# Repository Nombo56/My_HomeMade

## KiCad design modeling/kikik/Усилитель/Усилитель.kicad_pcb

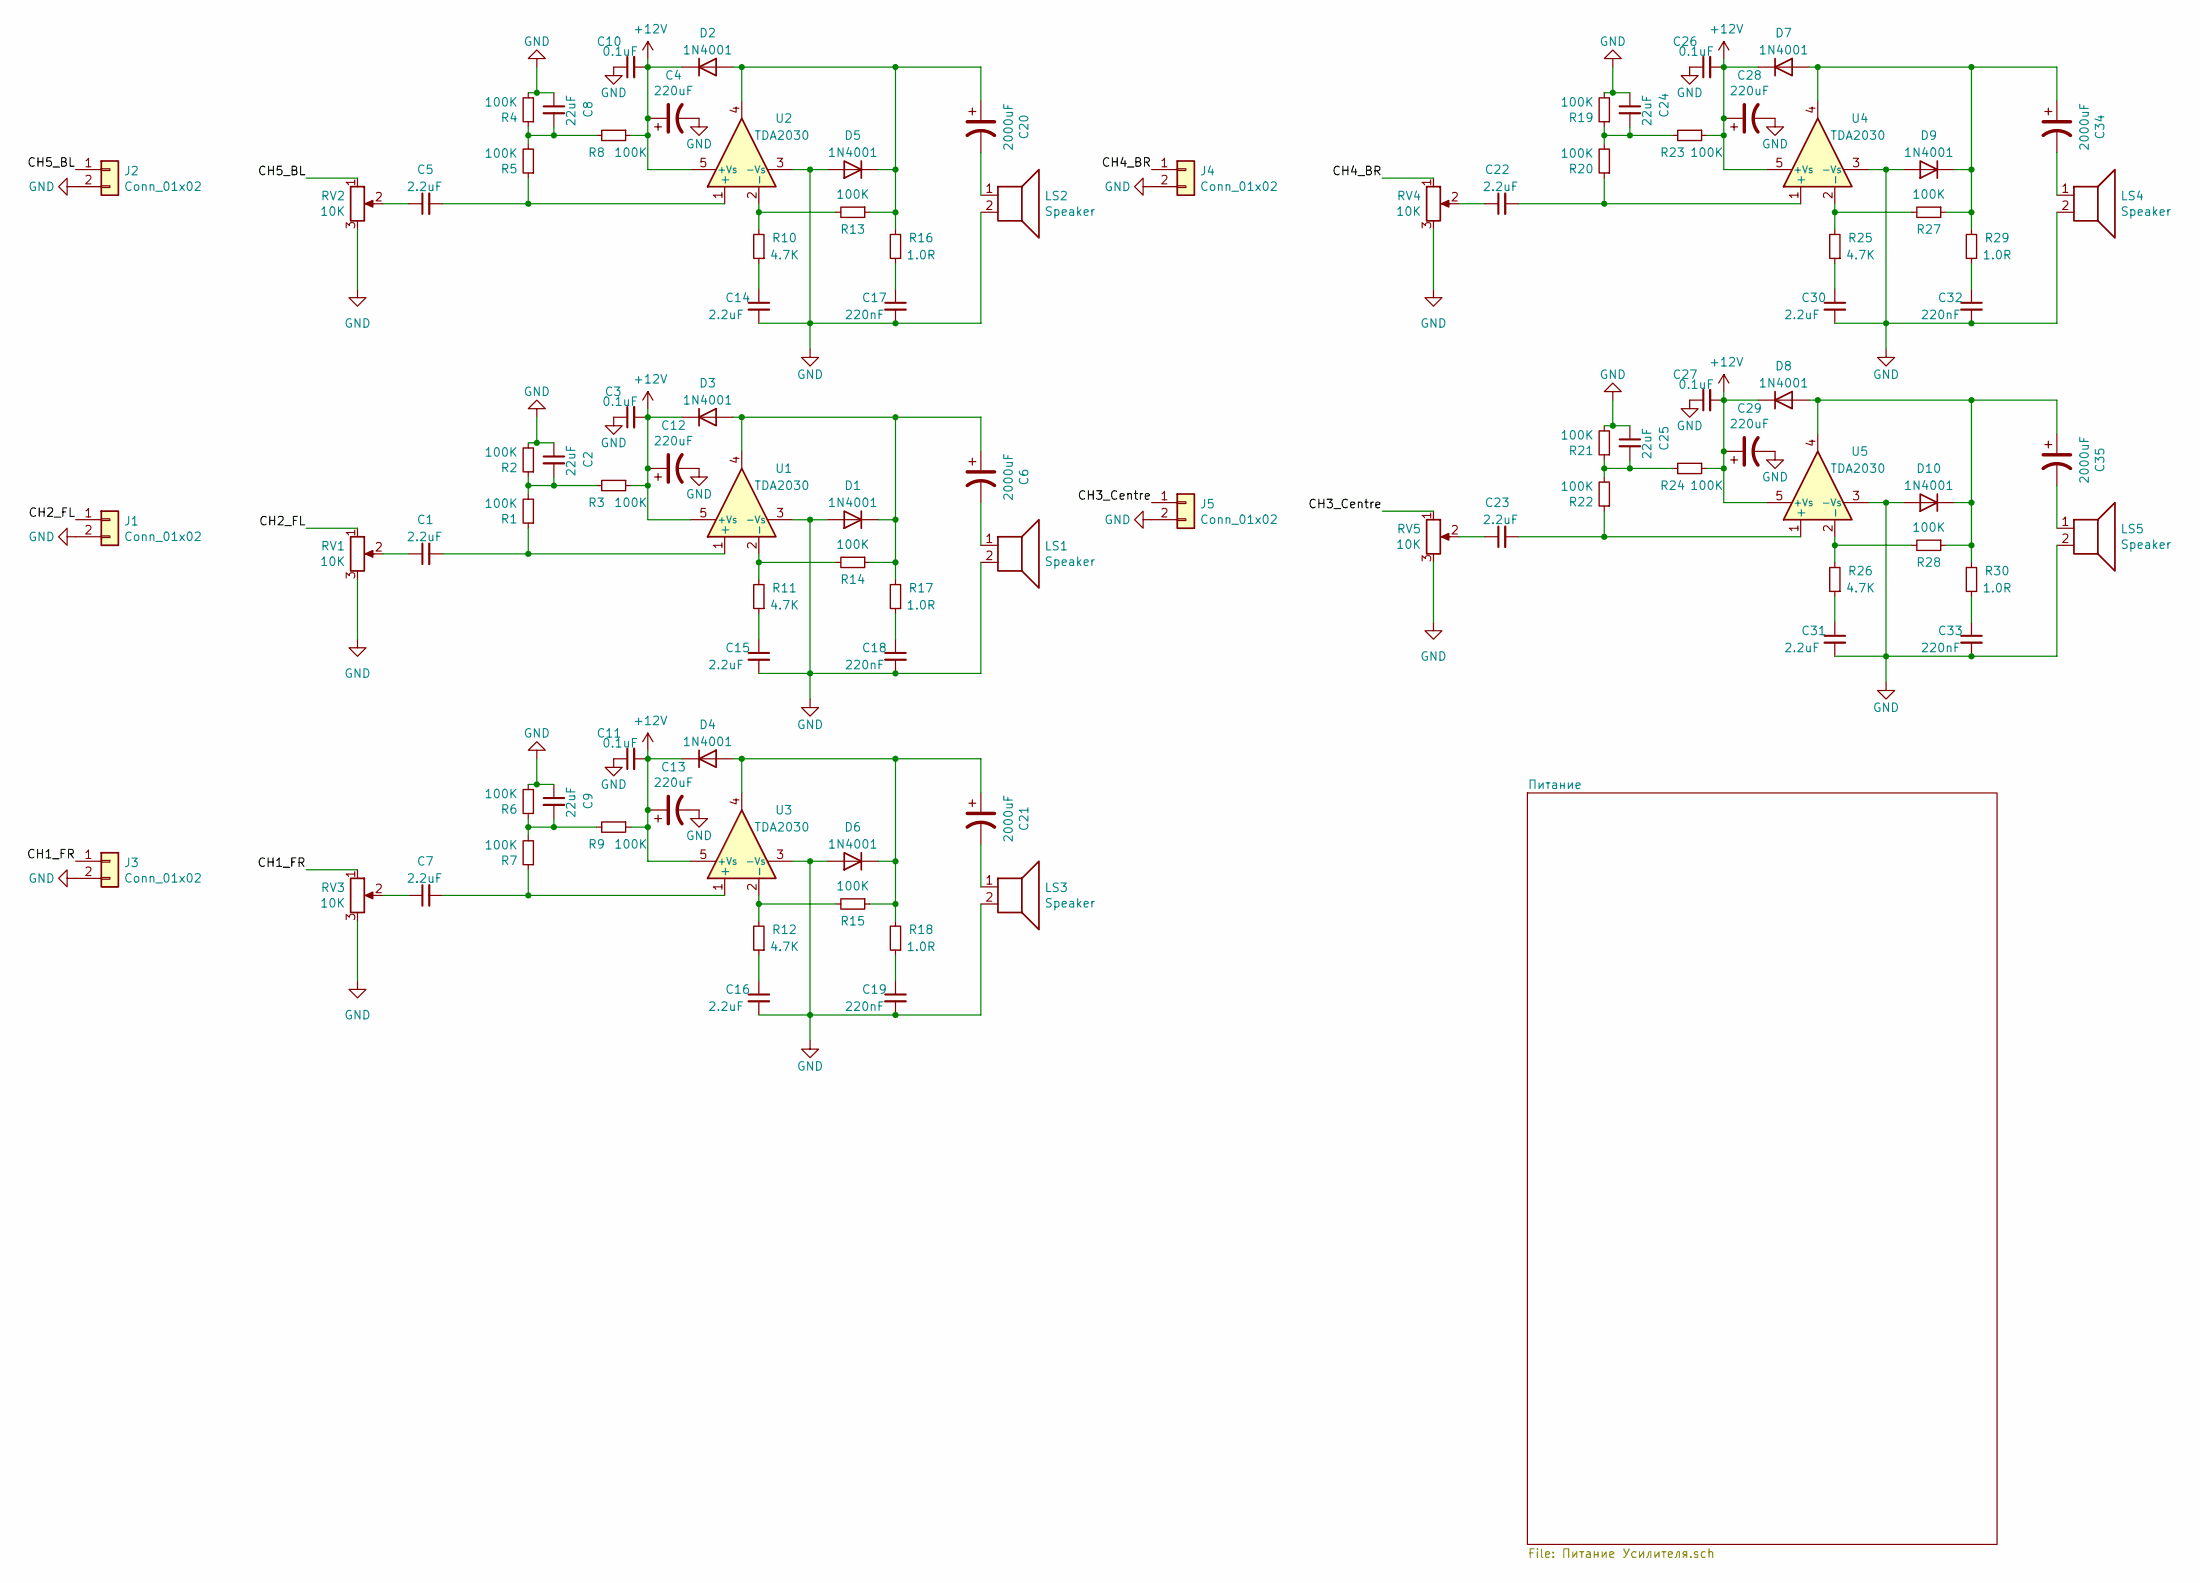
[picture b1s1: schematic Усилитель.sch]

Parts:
C1, C5, C7, C14, C15, C16, C22, C23, C30, C31: 2.2uF; C_0805_2012Metric
C2, C8, C9, C24, C25: 22uF; C_0805_2012Metric
C3, C10, C11, C26, C27: 0.1uF; C_0805_2012Metric
C4, C12, C13, C28, C29: 220uF; C_Elec_8x10.2
C6, C20, C21, C34, C35: 2000uF; CP_Radial_D13.0mm_P5.00mm
C17, C18, C19, C32, C33: 220nF; C_0805_2012Metric
D1, D2, D3, D4, D5, D6, D7, D8, D9, D10: 1N4001; D_DO-41_SOD81_P10.16mm_Horizontal
J1, J2, J3, J4, J5: Conn_01x02; PinHeader_1x02_P2.54mm_Vertical
LS1, LS2, LS3, LS4, LS5: Speaker; PinHeader_1x02_P2.54mm_Vertical
R1, R2, R3, R4, R5, R6, R7, R8, R9, R13, R14, R15, R19, R20, R21, R22, R23, R24, R27, R28: 100K; R_0805_2012Metric
R10, R11, R12, R25, R26: 4.7K; R_0805_2012Metric
R16, R17, R18, R29, R30: 1.0R; R_0805_2012Metric
RV1, RV2, RV3, RV4, RV5: 10K; PinHeader_1x03_P2.54mm_Vertical
U1, U2, U3, U4, U5: TDA2030; TO-220-5_P3.4x3.7mm_StaggerOdd_Lead3.8mm_Vertical

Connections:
/CH1_FR: J3.1, RV3.1
/CH2_FL: J1.1, RV1.1
/CH3_Centre: J5.1, RV5.1
/CH4_BR: J4.1, RV4.1
/CH5_BL: J2.1, RV2.1
GND: C2.1, C3.1, C4.2, C8.1, C9.1, C10.1, C11.1, C12.2, C13.2, C14.2, C15.2, C16.2, C17.2, C18.2, C19.2, C24.1, C25.1, C26.1, C27.1, C28.2, C29.2, C30.2, C31.2, C32.2, C33.2, D1.2 (A), D5.2 (A), D6.2 (A), D9.2 (A), D10.2 (A), J1.2, J2.2, J3.2, J4.2, J5.2, LS1.2, LS2.2, LS3.2, LS4.2, LS5.2, R2.2, R4.2, R6.2, R19.2, R21.2, RV1.3, RV2.3, RV3.3, RV4.3, RV5.3, U1.3 (-Vs), U2.3 (-Vs), U3.3 (-Vs), U4.3 (-Vs), U5.3 (-Vs); also elsewhere on the board
unnamed: C1.1, RV1.2
unnamed: C1.2, R1.1, U1.1 (+)
unnamed: C2.2, R1.2, R2.1, R3.2
unnamed: C5.1, RV2.2
unnamed: C5.2, R5.1, U2.1 (+)
unnamed: C6.1, D1.1 (K), D3.2 (A), R14.1, R17.2, U1.4
unnamed: C6.2, LS1.1
unnamed: C7.1, RV3.2
unnamed: C7.2, R7.1, U3.1 (+)
unnamed: C8.2, R4.1, R5.2, R8.2
unnamed: C9.2, R6.1, R7.2, R9.2
unnamed: C14.1, R10.1
unnamed: C15.1, R11.1
unnamed: C16.1, R12.1
unnamed: C17.1, R16.1
unnamed: C18.1, R17.1
unnamed: C19.1, R18.1
unnamed: C20.1, D2.2 (A), D5.1 (K), R13.1, R16.2, U2.4
unnamed: C20.2, LS2.1
unnamed: C21.1, D4.2 (A), D6.1 (K), R15.1, R18.2, U3.4
unnamed: C21.2, LS3.1
unnamed: C22.1, RV4.2
unnamed: C22.2, R20.1, U4.1 (+)
unnamed: C23.1, RV5.2
unnamed: C23.2, R22.1, U5.1 (+)
unnamed: C24.2, R19.1, R20.2, R23.2
unnamed: C25.2, R21.1, R22.2, R24.2
unnamed: C30.1, R25.1
unnamed: C31.1, R26.1
unnamed: C32.1, R29.1
unnamed: C33.1, R30.1
unnamed: C34.1, D7.2 (A), D9.1 (K), R27.1, R29.2, U4.4
unnamed: C34.2, LS4.1
unnamed: C35.1, D8.2 (A), D10.1 (K), R28.1, R30.2, U5.4
unnamed: C35.2, LS5.1
unnamed: R10.2, R13.2, U2.2 (-)
unnamed: R11.2, R14.2, U1.2 (-)
unnamed: R12.2, R15.2, U3.2 (-)
unnamed: R25.2, R27.2, U4.2 (-)
unnamed: R26.2, R28.2, U5.2 (-)

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
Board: 2 copper layers, 100 parts (0 on the bottom side), 47 nets, no tracks yet.

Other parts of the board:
C4#2, C12#2, C13#2, C28#2, C29#2: 220uF; C_0805_2012Metric

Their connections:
GND: C4#2.2, C12#2.2, C13#2.2, C28#2.2, C29#2.2; also elsewhere on the board

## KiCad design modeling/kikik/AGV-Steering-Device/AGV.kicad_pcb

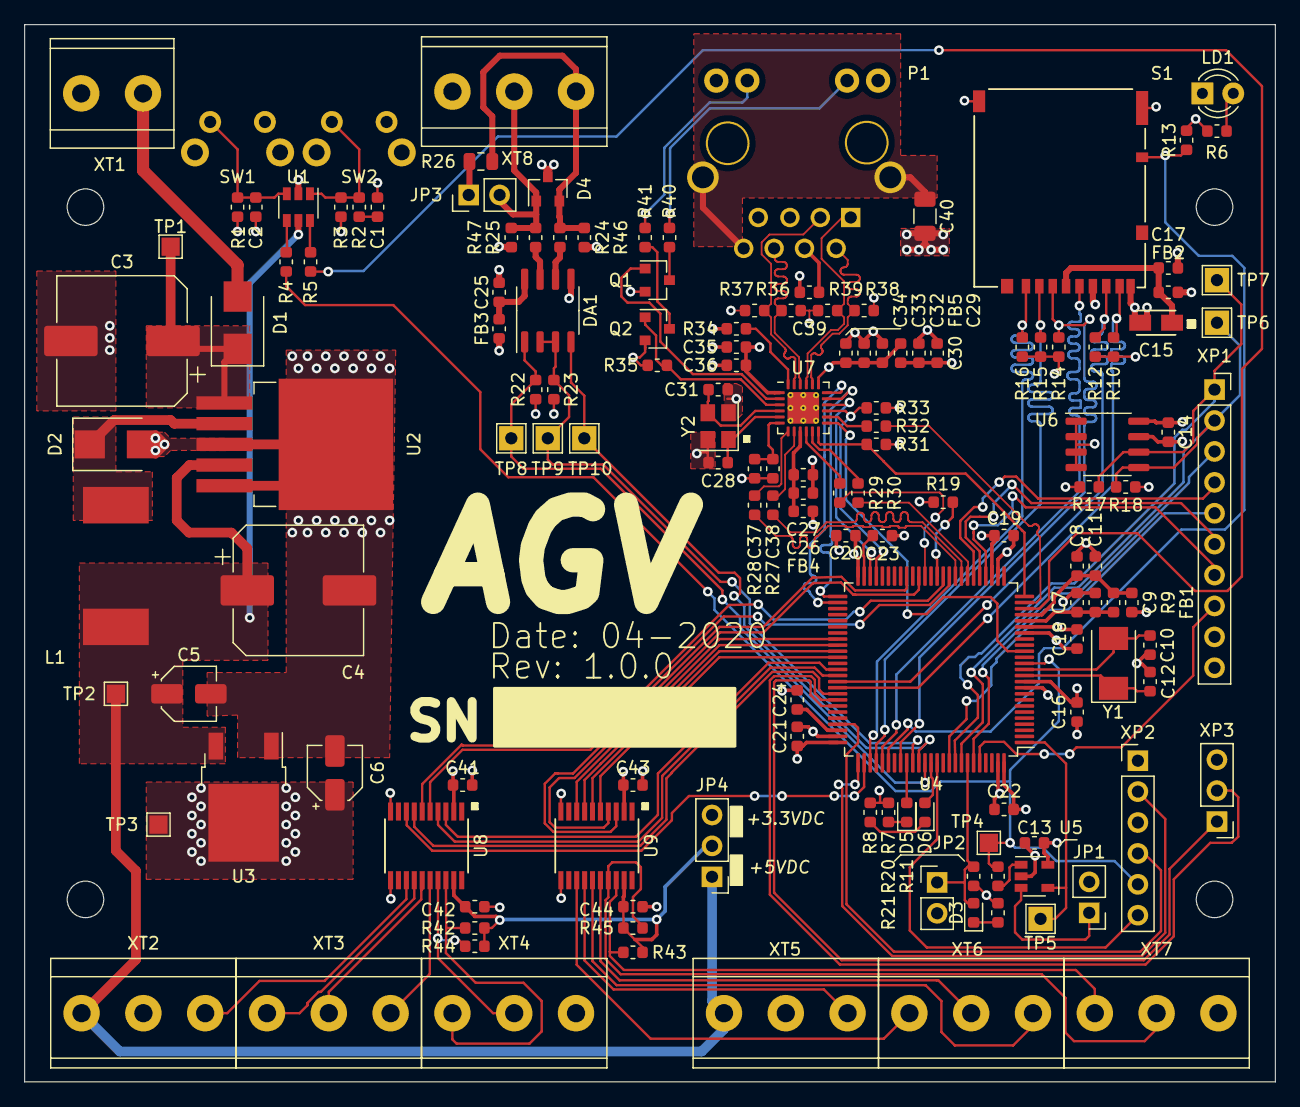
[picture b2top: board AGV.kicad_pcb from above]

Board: 4 copper layers, 102.8 x 86.9 mm, 147 parts (0 on the bottom side), 118 nets.

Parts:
C1, C2, C13, C14, C16, C17, C18, C19, C20, C21, C22, C25, C27, C30, C33, C35, C41, C42, C43, C44: 100n; C_0603_1608Metric
C3: 100uF; CP_Elec_10x10.5
C4: 330uF; CP_Elec_10x10.5
C5, C6: 10uF; CP_Elec_4x5.4
C7, C8, C34, C36: 10n; C_0603_1608Metric
C9, C11, C37: 1uF; C_0603_1608Metric
C10, C12: 27pF; C_0603_1608Metric
C15: 47uF; TantalSizeA
C23, C24: 2.2uF; C_0603_1608Metric
C26: 4.7uF; C_0603_1608Metric
C28, C31: 22pF; C_0603_1608Metric
C29, C32: 10uF; C_0603_1608Metric
C38: 470pF; C_0603_1608Metric
C39: 22n; C_0603_1608Metric
C40: 1n; C_1206_3216Metric
D1, D2: STPS3L60U; D_SMB
D3: KP-1608SURC; LED_0603_1608Metric
D4: CDSOT23-SM712; SOT-23
D5, D6: KP-1608MGC; LED_0603_1608Metric
DA1: SN65HVD1785D; SO-8_3.9x4.9mm_P1.27mm
FB1, FB2, FB3, FB4, FB5: 1000R @ 100 MHz; L_0603_1608Metric
JP1, JP2, JP3: NO; PinHeader_1x02_P2.54mm_Vertical
JP4: U8-U9 SIDE B POWER SUPPLY:; PinHeader_1x03_P2.54mm_Vertical
L1: 330uH; CDRH127
LD1: L-934GD; LED_D3.0mm
P1: HR911105A; HR911105
Q1, Q2: BSS138; SOT-23
R1, R22, R23, R33, R35: 10k; R_0603_1608Metric
R2: 100; R_0603_1608Metric
R3: 220k; R_0603_1608Metric
R4, R6, R7, R8, R11, R19, R20, R21: 1k; R_0603_1608Metric
R5: 330; R_0603_1608Metric
R9: 47; R_0603_1608Metric
R10, R12, R13, R14, R15, R16: 100k; R_0603_1608Metric
R17, R18, R42, R43, R44, R45: 4.7k; R_0603_1608Metric
R24, R25, R27, R28, R29, R30: 10R; R_0603_1608Metric
R26: 120; R_0805_2012Metric
R31: 1.5k; R_0603_1608Metric
R32: 33R; R_0603_1608Metric
R34: 12.1k; R_0603_1608Metric
R36, R37, R38, R39: 49R9; R_0603_1608Metric
R40, R41: 680; R_0603_1608Metric
R46, R47: DNP; R_0603_1608Metric
S1: DM3AT-SF-PEJM5
SW1, SW2: 1-1825027-7
TP1: VIN; TestPoint_Pad_1.5x1.5mm
TP2: +5VDC; TestPoint_Pad_1.5x1.5mm
TP3: +3.3VDC; TestPoint_Pad_1.5x1.5mm
TP4: ~NRESET; TestPoint_Pad_1.5x1.5mm
TP5: WDI; TestPoint_THTPad_2.0x2.0mm_Drill1.0mm
TP6: I2C_SDA; TestPoint_THTPad_2.0x2.0mm_Drill1.0mm
TP7: I2C_SCL; TestPoint_THTPad_2.0x2.0mm_Drill1.0mm
TP8: RS485-RX; TestPoint_THTPad_2.0x2.0mm_Drill1.0mm
TP9: RS485-~RE~\DE; TestPoint_THTPad_2.0x2.0mm_Drill1.0mm
TP10: RS485-TX; TestPoint_THTPad_2.0x2.0mm_Drill1.0mm
U1: USBLC6-2SC6; SOT-23-6
U2: LM2575HVS-5.0; TO-263-5Lead
U3: LD1086DT33TR; TO-252-2
U4: STM32F407VGTx; LQFP-100_14x14mm_P0.5mm
U5: STWD100NYWY3F; SOT-23-5
U6: AT24C256C-SSHL-T; SO-8_3.9x4.9mm_P1.27mm
U7: LAN8720AI-CP-TR; QFN-24-1EP_4x4mm_P0.5mm_EP2.6x2.6mm_ThermalVias
U8, U9: TXS0108EPW; TSSOP-20-P0.65-W6.5mm-H4.4mm-IPC7351-S-B
XP1: CONN-10F; PinSocket_1x10_P2.54mm_Vertical
XP2: PLS-6; PinHeader_1x06_P2.54mm_Vertical
XP3: PLS-3; PinHeader_1x03_P2.54mm_Vertical
XT1: 282841-2
XT2, XT3, XT4, XT5, XT6, XT7, XT8: 282841-3
Y1: 8MHz; Crystal_SMD_Abracon_ABM3-2Pin_5.0x3.2mm
Y2: 25.000 Mhz; Crystal_SMD_Geyer_KX-7T-4Pin_3.2x2.5mm

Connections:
+3.3VA: C32.1, C33.1, C34.1, C35.1, C36.1, C39.1, FB5.1, P1.4, P1.5, R36.1, R37.1, R38.1, R39.1, U7.1, U7.19
+3V3: C1.2, C6.1, C13.1, C14.1, C16.1, C18.1, C19.1, C20.1, C21.1, C22.1, C29.1, C30.1, C41.1, C43.1, FB1.2, FB2.2, FB3.1, FB4.2, FB5.2, JP1.2, JP2.2, JP4.3, P1.9, P1.12, R1.1, R6.1, R10.1, R12.1, R13.2, R14.1, R15.1, R16.1, R17.2, R18.2, R22.1, R31.1, R33.1, R46.2, SW2.2, TP3.1, U3.2, U4.11, U4.19, U4.28, U4.50, U4.75, U4.100, U5.5, U6.8, U8.2, U8.10, U9.2, U9.10, XP1.9, XP2.1
+5V: C4.1, C5.1, JP4.1, L1.2, TP2.1, U1.5, U2.4, U3.3, XT2.1, XT5.1
/ETHERNET/ETH_CRS_DV: R30.1, U4.32
/ETHERNET/ETH_DIO: R31.2, U4.25, U7.12
/ETHERNET/ETH_MDC: U4.16, U7.13
/ETHERNET/ETH_REF_CLK: R32.1, U4.24
/ETHERNET/ETH_RXD0: R27.1, U4.33
/ETHERNET/ETH_RXD1: R28.1, U4.34
/ETHERNET/ETH_RXERR: R29.1, U4.39
/ETHERNET/ETH_TXD0: U4.51, U7.17
/ETHERNET/ETH_TXD1: U4.52, U7.18
/ETHERNET/ETH_TXEN: U4.48, U7.16
/ETHERNET/ETH_~NRST: R33.2, U4.47, U7.15
/ETHERNET/LED1_LINK_ACT: Q2.1, R35.1, U7.3
/ETHERNET/LED2_SPEED: Q1.1, U7.2
/ETHERNET/RX+: P1.3, R37.2, U7.23
/ETHERNET/RX-: P1.6, R36.2, U7.22
/ETHERNET/TX+: P1.1, R39.2, U7.21
/ETHERNET/TX-: P1.2, R38.2, U7.20
/ETHERNET/VDDCR: C37.1, C38.1, U7.6
/IO/A-ENC1_SA: U4.63, U8.3
/IO/A-ENC1_SB: R42.2, U8.18, XT4.1
/IO/A-ENC2_SA: U4.42, U9.3
/IO/A-ENC2_SB: R43.2, U9.18, XT7.1
/IO/B-ENC1_SA: U4.64, U8.4
/IO/B-ENC1_SB: R44.2, U8.17, XT4.2
/IO/B-ENC2_SA: U4.40, U9.4
/IO/B-ENC2_SB: R45.2, U9.17, XT7.2
/IO/LEN-IBT1-SA: U4.67, U8.7
/IO/LEN-IBT1-SB: U8.14, XT3.1
/IO/LEN-IBT2-SA: U4.58, U9.8
/IO/LEN-IBT2-SB: U9.13, XT6.1
/IO/LPWM-IBT1-SA: U4.35, U8.5
/IO/LPWM-IBT1-SB: U8.16, XT3.3
/IO/LPWM-IBT2-SA: U4.60, U9.6
/IO/LPWM-IBT2-SB: U9.15, XT6.3
/IO/REN-IBT1-SA: U4.77, U8.8
/IO/REN-IBT1-SB: U8.13, XT2.3
/IO/REN-IBT2-SA: U4.59, U9.7
/IO/REN-IBT2-SB: U9.14, XT5.3
/IO/RPWM-IBT1-SA: U4.36, U8.6
/IO/RPWM-IBT1-SB: U8.15, XT3.2
/IO/RPWM-IBT2-SA: U4.61, U9.5
/IO/RPWM-IBT2-SB: U9.16, XT6.2
/IO/VCCB: C42.1, C44.1, JP4.2, R42.1, R43.1, R44.1, R45.1, U8.19, U9.19
/MCU/BOOT0: D3.2, JP2.1, R20.2, U4.94
/MCU/BOOT1: R19.2, U4.37
/MCU/EXT-GPIO1: U4.96, XP1.8
/MCU/EXT-I2C-SCL: R17.1, TP7.1, U4.92, U6.6, XP1.1
/MCU/EXT-I2C-SDA: R18.1, TP6.1, U4.93, U6.5, XP1.2
/MCU/EXT-I2C-~INT: U4.95, XP1.3
/MCU/EXT-SPI-CS: U4.29, XP1.7
/MCU/EXT-SPI-MISO: U4.31, XP1.4
/MCU/EXT-SPI-MOSI: U4.91, XP1.5
/MCU/EXT-SPI-SCK: U4.30, XP1.6
/MCU/RS485-RX: DA1.1, R22.2, TP8.1, U4.87
/MCU/RS485-TX: DA1.4, TP10.1, U4.86
/MCU/RS485-~RE~\DE: DA1.2, DA1.3, R23.1, TP9.1, U4.85
/MCU/SDIO_CLK: S1.5, U4.80
/MCU/SDIO_CMD: R14.2, S1.3, U4.83
/MCU/SDIO_DAT0: R12.2, S1.7, U4.65
/MCU/SDIO_DAT1: R10.2, S1.8, U4.66
/MCU/SDIO_DAT2: R16.2, S1.1, U4.78
/MCU/SDIO_DAT3: R15.2, S1.2, U4.79
/MCU/SWCLK: U4.76, XP2.2
/MCU/SWDIO: U4.72, XP2.4
/MCU/SWO: U4.89, XP2.6
/MCU/USART_1_RX: U4.69, XP3.1
/MCU/USART_1_TX: U4.68, XP3.2
/MCU/USER_LED1: D5.2, U4.84
/MCU/USER_LED2: D6.2, U4.88
/MCU/USR_BTN: R5.2, U4.23
/MCU/VCAP_1: C23.1, U4.49
/MCU/VCAP_2: C24.1, U4.73
/MCU/WDI: TP5.1, U4.1, U5.4
/MCU/~NRESET: R4.2, R11.2, TP4.1, U4.14, XP2.5
/MCU/~SDIO_CDET: R13.1, S1.9, U4.81
/POWER/VIN: D1.2, XT1.1
/RS-485/RS-485-A: D4.2, R24.1, R26.1, R46.1, XT8.1
/RS-485/RS-485-B: D4.1, JP3.2, R25.1, R47.2, XT8.2
GND: C2.2, C3.2, C4.2, C5.2, C6.2, C7.2, C8.2, C9.2, C10.2, C11.2, C12.2, C13.2, C14.2, C15.2, C16.2, C17.2, C18.2, C19.2, C20.2, C21.2, C22.2, C23.2, C24.2, C25.2, C26.2, C27.2, C28.2, C29.2, C30.2, C31.2, C32.2, C33.2, C34.2, C35.2, C36.2, C37.2, C38.2, C39.2, C40.2, C41.2, C42.2, C43.2, C44.2, D2.2, D4.3, DA1.5, LD1.1, Q1.2, Q2.2, R3.2, R7.1, R8.1, R19.1, R20.1, R21.1, R23.2, R34.2, R35.2, R47.1, S1.6, S1.10, SW1.2, SW1.3, SW1.4, SW2.3, SW2.4, U1.2, U2.3, U2.5, U3.1, U4.10, U4.20, U4.27, U4.74, U4.99, U5.2, U6.1, U6.2, U6.3, U6.4, U6.7, U7.25, U8.11, U9.11, XP1.10, XP2.3, XP3.3, XT1.2, XT2.2, XT4.3, XT5.2, XT7.3, XT8.3, Y2.2, Y2.4
unnamed: C1.1, R2.1
unnamed: C2.1, R1.2, SW1.1, U1.3
unnamed: C3.1, D1.1, TP1.1, U2.1
unnamed: C7.1, C9.1, R9.1, U4.21
unnamed: C10.1, U4.13, Y1.2
unnamed: C8.1, C11.1, FB1.1, R9.2, U4.22
unnamed: C12.1, U4.12, Y1.1
unnamed: C15.1, C17.1, FB2.1, S1.4
unnamed: C25.1, DA1.8, FB3.2
unnamed: C28.1, U7.5, Y2.1
unnamed: C31.1, U7.4, Y2.3
unnamed: C40.1, P1.8
unnamed: D2.1, L1.1, U2.2
unnamed: D3.1, R21.2
unnamed: D5.1, R7.2
unnamed: D6.1, R8.2
unnamed: DA1.6, R24.2
unnamed: DA1.7, R25.2
unnamed: JP1.1, U5.3
unnamed: JP3.1, R26.2
unnamed: LD1.2, R6.2
unnamed: P1.10, R40.2
unnamed: P1.11, R41.2
unnamed: Q1.3, R40.1
unnamed: Q2.3, R41.1
unnamed: R2.2, R3.1, SW2.1, U1.1
unnamed: R4.1, U1.4
unnamed: R5.1, U1.6
unnamed: R11.1, U5.1
unnamed: R27.2, U7.8
unnamed: R28.2, U7.7
unnamed: R29.2, U7.10
unnamed: R30.2, U7.11
unnamed: R32.2, U7.14
unnamed: R34.1, U7.24
VDD: C26.1, C27.1, FB4.1, U7.9
